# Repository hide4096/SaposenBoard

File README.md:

# サポセンボード

Nucleoボード(https://www.st.com/ja/evaluation-tools/nucleo-f303k8.html) をさして使える電子工作ボード

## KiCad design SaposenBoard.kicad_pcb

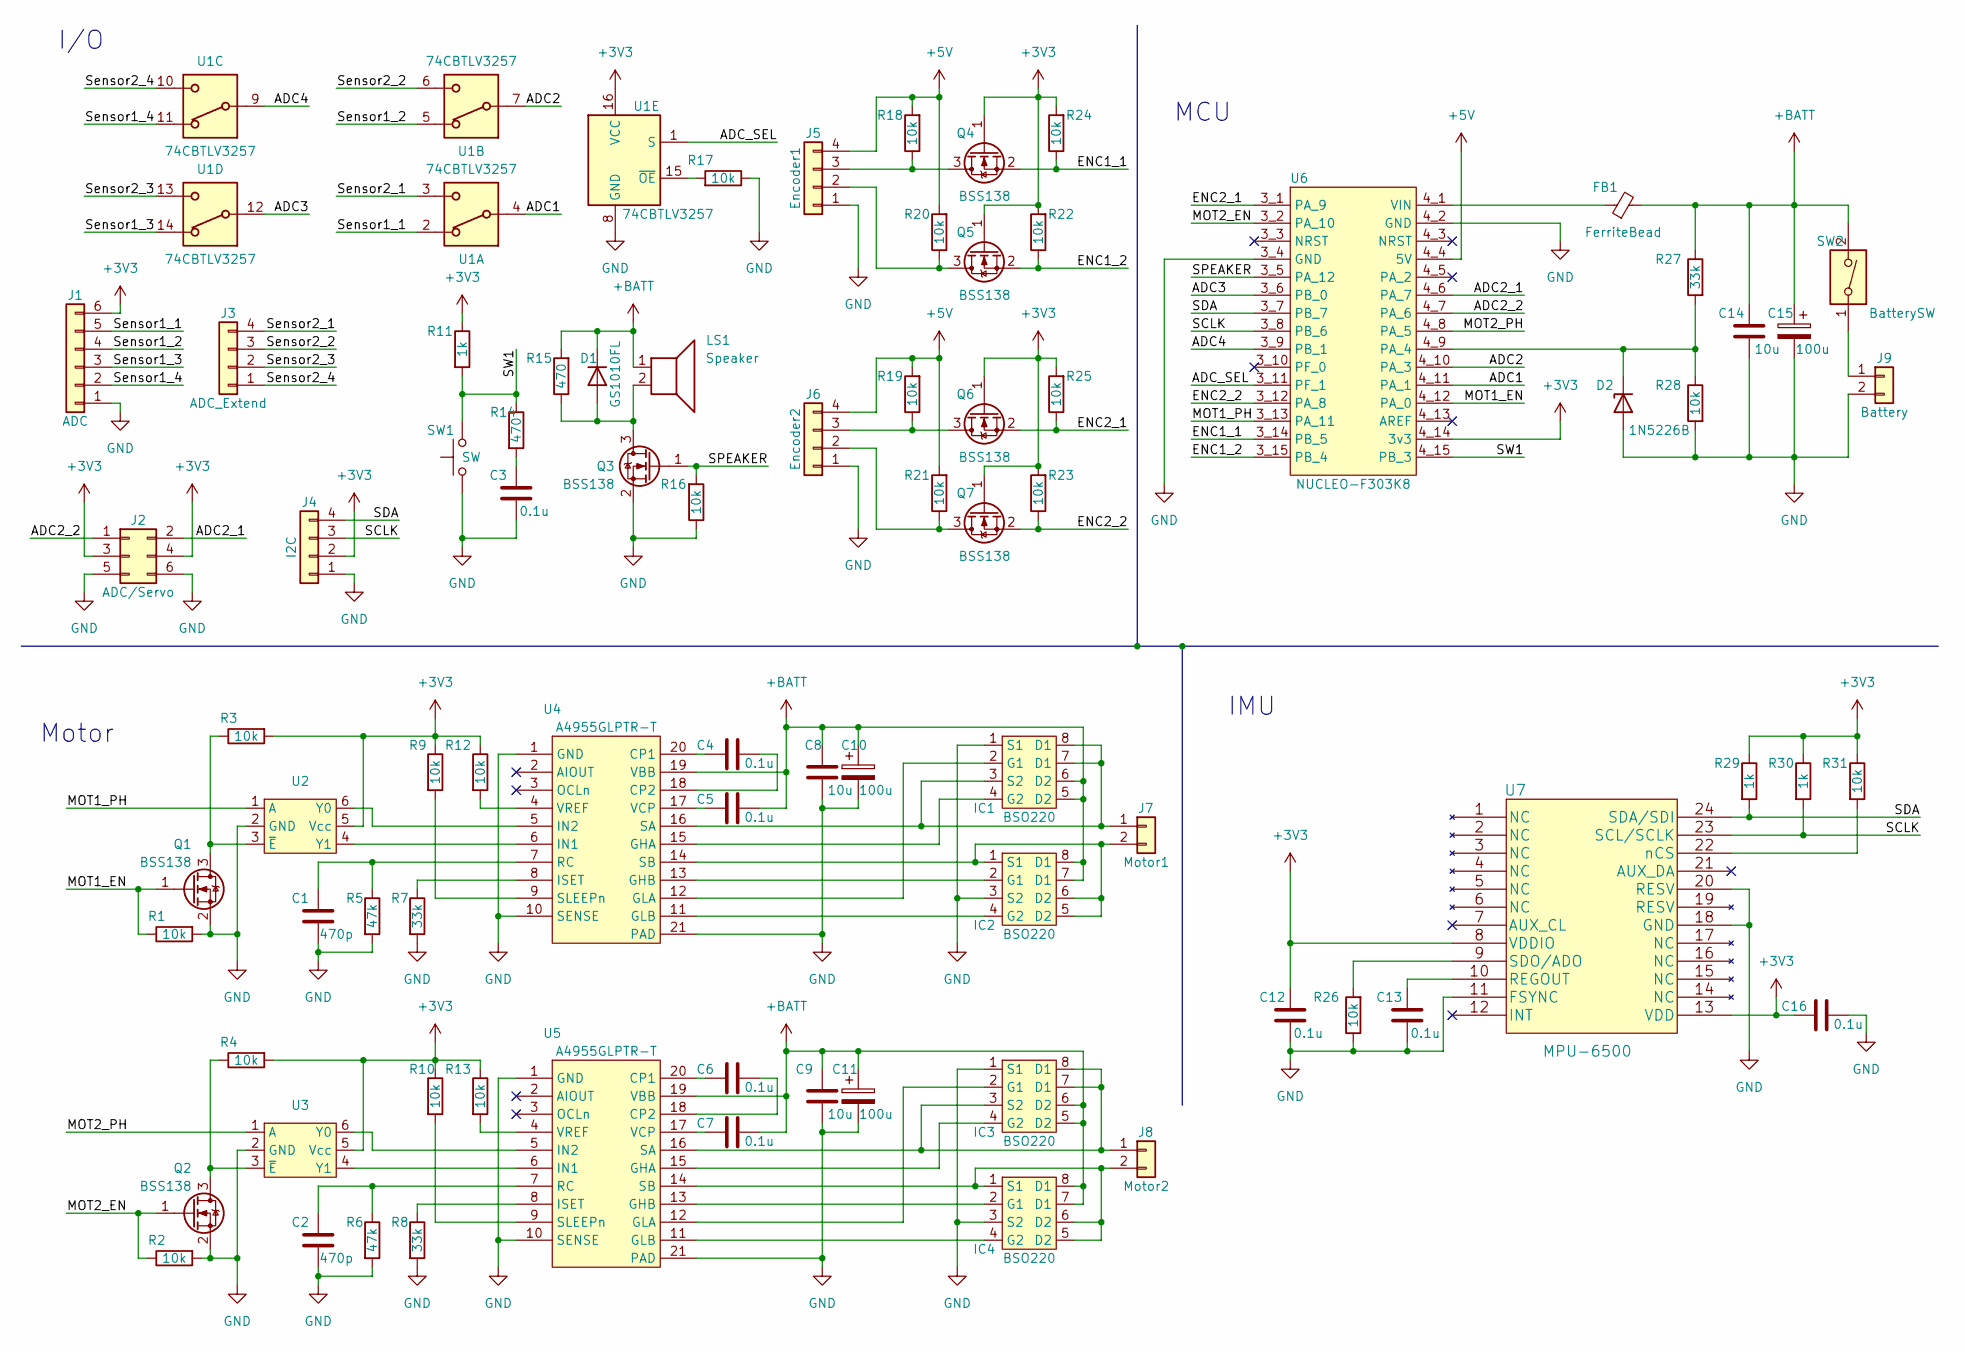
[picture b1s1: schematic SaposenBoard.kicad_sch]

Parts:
C1, C2: 470p; C_0603_1608Metric
C3, C4, C5, C6, C7, C12, C13, C16: 0.1u; C_0603_1608Metric
C8, C9, C14: 10u; C_0805_2012Metric
C10, C11, C15: 100u; CP_Radial_D5.0mm_P2.50mm
D1: GS1010FL; D_SOD-123F
D2: 1N5226B; D_DO-35_SOD27_P2.54mm_Vertical_KathodeUp
FB1: FerriteBead; L_0603_1608Metric
IC1, IC2, IC3, IC4: BSO220; BSO220N03MD
J1: ADC; Molex_Micro-Latch_53253-0670_1x06_P2.00mm_Vertical
J2: ADC/Servo; PinHeader_2x03_P2.54mm_Vertical
J3: ADC_Extend; Molex_Micro-Latch_53253-0470_1x04_P2.00mm_Vertical
J4: I2C; PinHeader_1x04_P2.54mm_Vertical
J5: Encoder1; Molex_Micro-Latch_53253-0470_1x04_P2.00mm_Vertical
J6: Encoder2; Molex_Micro-Latch_53253-0470_1x04_P2.00mm_Vertical
J7: Motor1; CONN_B02B-PASKLFSN_JST
J8: Motor2; CONN_B02B-PASKLFSN_JST
J9: Battery; IL-G_2P
LS1: Speaker; PKM13EPYH4000-A0
Q1, Q2, Q3, Q4, Q5, Q6, Q7: BSS138; SOT-23
R1, R2, R3, R4, R9, R10, R12, R13, R16, R17, R18, R19, R20, R21, R22, R23, R24, R25, R26, R28, R31: 10k; R_0603_1608Metric
R5, R6: 47k; R_0603_1608Metric
R7, R8, R27: 33k; R_0603_1608Metric
R11, R29, R30: 1k; R_0603_1608Metric
R14, R15: 470; R_0603_1608Metric
SW1: SW; TVDT18-050C
SW2: BatterySW; 2MS1-T1-B4-VS2-Q-E-S
U1: 74CBTLV3257; TSSOP-16_4.4x5mm_P0.65mm
U2, U3: SOT-363_SC-70-6
U4, U5: A4955GLPTR-T
U6: NUCLEO-F303K8; MODULE_NUCLEO-F303K8
U7: MPU-6500; QFN40P300X300X95-25N-D

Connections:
+3V3: C12.1, C16.1, J1.6, J2.3, J2.4, J4.2, Q4.1 (G), Q5.1 (G), Q6.1 (G), Q7.1 (G), R3.2, R4.2, R9.1, R10.1, R11.1, R12.1, R13.1, R22.2, R23.2, R24.2, R25.2, R29.1, R30.1, R31.1, U1.16 (VCC), U2.5 (Vcc), U3.5 (Vcc), U6.4_14 (3v3), U7.8 (VDDIO), U7.13 (VDD)
+5V: J5.4, J6.4, R18.2, R19.2, R20.2, R21.2, U6.4_4 (5V)
+BATT: C5.2, C7.2, C8.2, C9.2, C10.1, C11.1, C14.2, C15.1, D1.1 (K), FB1.2, IC1.5 (D2), IC1.6 (D2), IC2.7 (D1), IC2.8 (D1), IC3.5 (D2), IC3.6 (D2), IC4.7 (D1), IC4.8 (D1), LS1.1, R15.2, R27.1, SW2.2, U4.19 (VBB), U5.19 (VBB)
/ADC1: U1.4, U6.4_11 (PA_1)
/ADC2: U1.7, U6.4_10 (PA_3)
/ADC2_1: J2.2, U6.4_6 (PA_7)
/ADC2_2: J2.1, U6.4_7 (PA_6)
/ADC3: U1.12, U6.3_6 (PB_0)
/ADC4: U1.9, U6.3_9 (PB_1)
/ADC_SEL: U1.1 (S), U6.3_11 (PF_1)
/ENC1_1: Q4.2 (S), R24.1, U6.3_14 (PB_5)
/ENC1_2: Q5.2 (S), R22.1, U6.3_15 (PB_4)
/ENC2_1: Q6.2 (S), R25.1, U6.3_1 (PA_9)
/ENC2_2: Q7.2 (S), R23.1, U6.3_12 (PA_8)
/MOT1_EN: Q1.1 (G), R1.1, U6.4_12 (PA_0)
/MOT1_PH: U2.1 (A), U6.3_13 (PA_11)
/MOT2_EN: Q2.1 (G), R2.1, U6.3_2 (PA_10)
/MOT2_PH: U3.1 (A), U6.4_8 (PA_5)
/SCLK: J4.3, R30.2, U6.3_8 (PB_6), U7.23 (SCL/SCLK)
/SDA: J4.4, R29.2, U6.3_7 (PB_7), U7.24 (SDA/SDI)
/SPEAKER: Q3.1 (G), R16.2, U6.3_5 (PA_12)
/SW1: R11.2, R14.1, SW1.2, U6.4_15 (PB_3)
/Sensor1_1: J1.5, U1.2
/Sensor1_2: J1.4, U1.5
/Sensor1_3: J1.3, U1.14
/Sensor1_4: J1.2, U1.11
/Sensor2_1: J3.4, U1.3
/Sensor2_2: J3.3, U1.6
/Sensor2_3: J3.2, U1.13
/Sensor2_4: J3.1, U1.10
GND: C1.2, C2.2, C3.2, C8.1, C9.1, C10.2, C11.2, C12.2, C13.2, C14.1, C15.2, C16.2, D2.2 (A), IC1.1 (S1), IC2.3 (S2), IC3.1 (S1), IC4.3 (S2), J1.1, J2.5, J2.6, J4.1, J5.1, J6.1, J9.2, Q1.2 (S), Q2.2 (S), Q3.2 (S), R1.2, R2.2, R5.2, R6.2, R7.2, R8.2, R16.1, R17.1, R26.1, R28.2, SW1.1, U1.8 (GND), U2.2 (GND), U3.2 (GND), U4.1 (GND), U4.10 (SENSE), U4.21 (PAD), U5.1 (GND), U5.10 (SENSE), U5.21 (PAD), U6.3_4 (GND), U6.4_2 (GND), U7.11 (FSYNC), U7.18 (GND), U7.20 (RESV)
unnamed: C3.1, R14.2
unnamed: D1.2 (A), LS1.2, Q3.3 (D), R15.1
unnamed: D2.1 (K), R27.2, R28.1, U6.4_9 (PA_4)
unnamed: IC1.2 (G1), U4.12 (GLA)
unnamed: IC1.4 (G2), U4.15 (GHA)
unnamed: IC1.3 (S2), IC1.7 (D1), IC1.8 (D1), J7.1, U4.16 (SA)
unnamed: IC2.2 (G1), U4.13 (GHB)
unnamed: IC2.4 (G2), U4.11 (GLB)
unnamed: IC2.1 (S1), IC2.5 (D2), IC2.6 (D2), J7.2, U4.14 (SB)
unnamed: IC3.2 (G1), U5.12 (GLA)
unnamed: IC3.4 (G2), U5.15 (GHA)
unnamed: IC3.3 (S2), IC3.7 (D1), IC3.8 (D1), J8.1, U5.16 (SA)
unnamed: IC4.2 (G1), U5.13 (GHB)
unnamed: IC4.4 (G2), U5.11 (GLB)
unnamed: IC4.1 (S1), IC4.5 (D2), IC4.6 (D2), J8.2, U5.14 (SB)
unnamed: J5.2, Q5.3 (D), R20.1
unnamed: J5.3, Q4.3 (D), R18.1
unnamed: J6.2, Q7.3 (D), R21.1
unnamed: J6.3, Q6.3 (D), R19.1
unnamed: J9.1, SW2.1
unnamed: Q1.3 (D), R3.1, U2.3 (~E)
unnamed: Q2.3 (D), R4.1, U3.3 (~E)
unnamed: R17.2, U1.15 (~OE)
unnamed: U2.6 (Y0), U4.5 (IN2)
unnamed: U2.4 (Y1), U4.6 (IN1)
unnamed: U3.6 (Y0), U5.5 (IN2)
unnamed: U3.4 (Y1), U5.6 (IN1)
unnamed: C4.1, U4.20 (CP1)
unnamed: C4.2, U4.18 (CP2)
unnamed: R7.1, U4.8 (ISET)
unnamed: C1.1, R5.1, U4.7 (RC)
unnamed: R9.2, U4.9 (SLEEPn)
unnamed: C5.1, U4.17 (VCP)
unnamed: R12.2, U4.4 (VREF)
unnamed: C6.1, U5.20 (CP1)
unnamed: C6.2, U5.18 (CP2)
unnamed: R8.1, U5.8 (ISET)
unnamed: C2.1, R6.1, U5.7 (RC)
unnamed: R10.2, U5.9 (SLEEPn)
unnamed: C7.1, U5.17 (VCP)
unnamed: R13.2, U5.4 (VREF)
unnamed: FB1.1, U6.4_1 (VIN)
unnamed: C13.1, U7.10 (REGOUT)
unnamed: R26.2, U7.9 (SDO/ADO)
unnamed: R31.2, U7.22 (nCS)

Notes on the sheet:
IMU
I/O
Motor
MCU

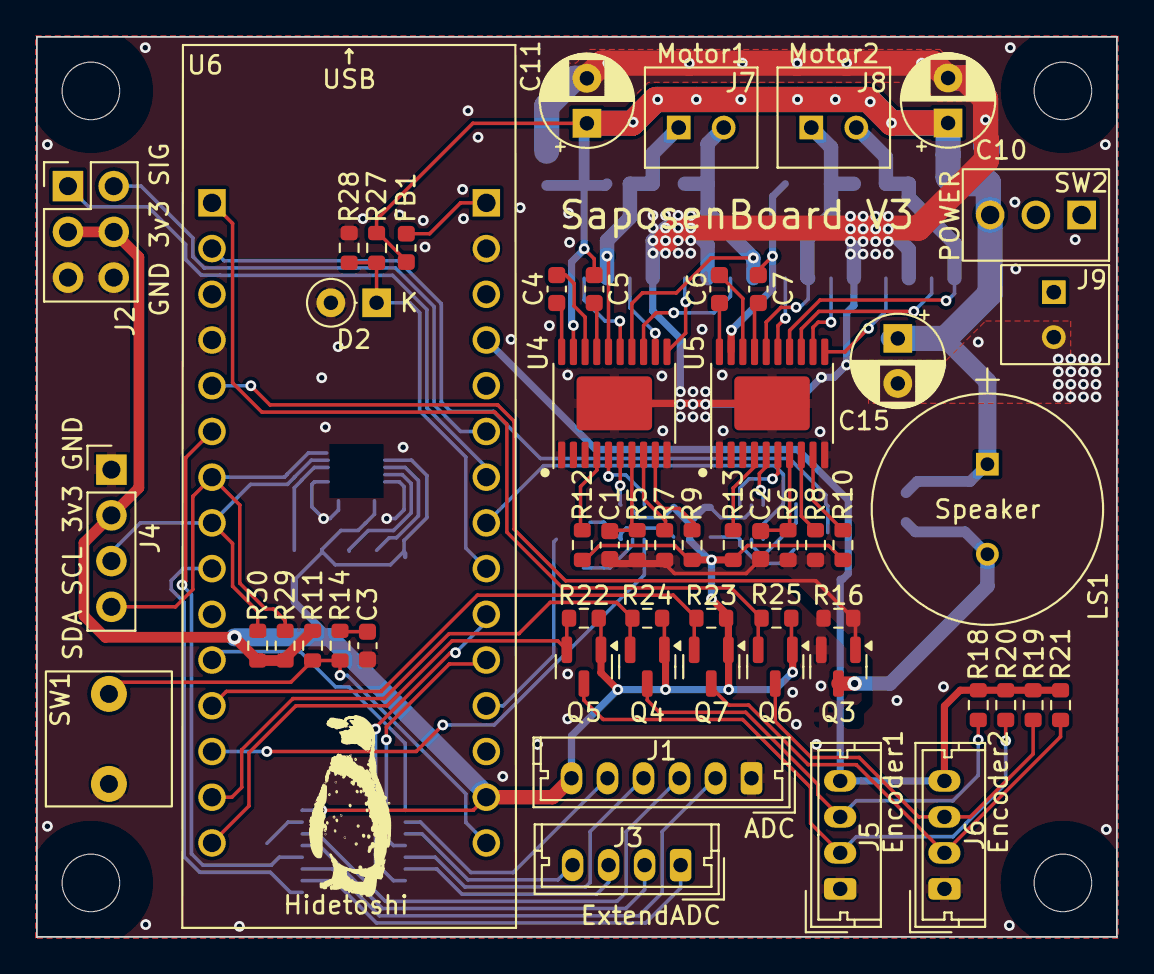
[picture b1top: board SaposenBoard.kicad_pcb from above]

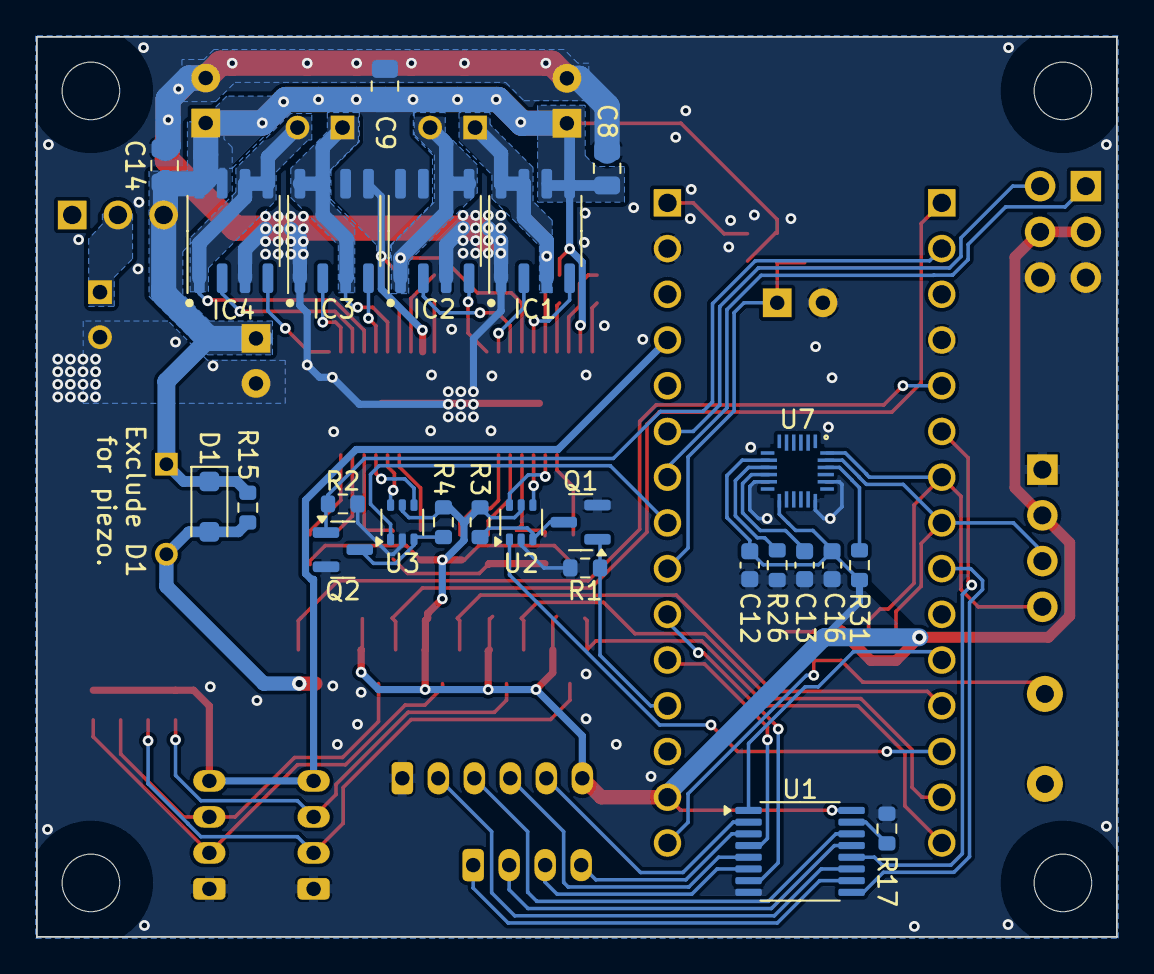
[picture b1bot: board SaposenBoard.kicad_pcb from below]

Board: 2 copper layers, 60.0 x 50.0 mm, 80 parts (25 on the bottom side), 76 nets.

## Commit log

2023-04-12 firstcommit
2023-04-12 [fix]Change path
2023-04-12 [add]配線始めた
2023-04-14 [add]配線とりあえず終わった
2023-04-14 [fix]シルク整えた
2023-04-15 [fix]ベタGND整備
2023-04-15 [update]チェックもらった
2023-04-15 [update]終わった
2023-04-18 [fix]コネクタの向きを修正
2023-04-18 [add]ガーバー更新
2023-04-21 [update]BOM出力
2023-05-10 V1.0
2023-05-10 [fix]IMUを裏に移動
2023-05-23 [add]なんか足した
2023-06-03 [add]配線できた
2023-06-05 [update]アンテナ除去
2023-06-12 [update]IMU位置見直し
2024-01-28 [fix]部品を変更
2024-01-28 [add]BOMファイル追加
2024-01-28 SupportCentorV2
2024-01-28 [add]ロゴ変更
2024-02-20 [update]回路図PDF更新
2024-03-12 [update]モータードライバの入力を変換
2024-03-12 [update]部品置いた
2024-03-12 [update]フットプリントを調整

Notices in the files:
parts and their libraries:
Copyright 2021 Accelerated Designs. All rights reserved.
